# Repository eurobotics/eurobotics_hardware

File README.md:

# EuRobotics Engineering Hardware
Hardware del equipo Eurobotics Engineering para el desarrollo de robots participantes en Eurobot.

## Organización

 - Cada carpeta del repositorio se corresponde con una tarjeta.

 - En el root de cada capeta se encuentra el proyecto de desarrollo de la tarjeta (Eagle, Orcad, Altium...). Si es una tarjeta comercial la documentación dada por el fabricante.

 - Por lo general, los archivos de cada proyecto se nombran como MMMMM_rXX, donde XX es la revisión y MMMMM el nombre de la tarjeta. La modificaciones sobre tarjetas fabricadas se documentan añadiendo al nombre del fichero de diseño el sufijo _NNNN_rYY_, donde NNNN es el identificador de la modificacion y YY es el número revisión de la modificación. Por ejemplo: "mainboard_r15_eurobot2012_r1.pdf" es la modificación para eurobot 2012 con revisión 1 de la tarjeta mainboard correspondientes a la revisión 15 de los esquemas.

 - Cada carpeta de una tarjeta desarrollada puede contener las siguientes subcarpetas:
   + bom: listado de materiales.
   + cam: ficheros de fabricación y versión en pdf de versiones de tarjetas fabricadas o de modificaciones en placa realizadas para una edición concreta de Eurobot.

## dsPIC Protoboard

Tarjeta prototipo basada en microcontrolador dspic33. Desarrollada para Eurobot 2010. Diseñada en Eagle (sólo esquematicos). Fabricada sobre tarjeta de prototipos. Es la tarjeta que se utilizó en el robot prototipo, llamado Dumybot, con el que se portó las librerías Aversive.

### Características

* Control motores: DC, Dunkermotoren, servos, AX12.
* Comunicaciones: RS-232, BT, SPI, I2C
* Sensores: industriales, TTL, laser analógico y encoders en cuadratura
* GPIOS: puerto de expansión I2C de 16 E/S.

### Autor

Javier Baliñas Santos

## Mainboard V01/V02

Tarjeta principal del robot. Compuesta por dos microcontroladores dspic33 comunicados por I2C, un maestro y un esclavo. El maestro está pensado para implementar la navegación motriz y estrategia del robot, y el
esclavo para controlar la mecánica del robot.

Desarrollada para el robot de Eurobot 2010. Diseño en Eagle (esquemáticos y PCB). Tiene varios bugs documentados y solucionados en la versión 2.

La versión V02 de la tarjeta principal soluciona algunos errores de la versión V01. Desarrollada para Eurobot 2012 y utilizada en las ediciones posteriores.

### Características

* 3 motores Dunkermotoren
* 2 motores DC de 12V
* 1 solenoide 12V
* 1 relé
* 2 telémetros lásers
* 5 servos estándar
* 1 interfaz servos AX12
* 3 encoders con salida en cuadratura
* 7 sensores 12V
* 1 interfaz RS-232
* 2 interfaces Bluetooth (SPP)
* 1 conector para tarjeta de sensores _sensorboard_

### Autor

Javier Baliñas Santos

## Mainboard V03

Tercera versión de la tarjeta principal de los robots. Compuesta por un único un microcontrolador.

Desarrollada para Eurobot 2014 y utilizada en las ediciones posteriores.

### Características
* 3 motores DC de 12V
* 4 servos estándar
* 1 interfaz servos AX12
* 2 encoders con salida en cuadratura
* 1 encoder con salida en cuadratura (módulo x4, sin decodificación de signo)
* 16 E/S de 12/5V
* 2 entradas de captura de tiempo
* 1 interfaz RS-232/Bluetooth
* 1 interfaz I2C
* 1 interfaz SPI

### Autores

Diseño electrónico: Javier Baliñas Santos  
Diseño PCB: Rubén Espino San José

## Sensorboard

Tarjeta de expansión E/S digital por I2C (32 E/S). Desarrollada para Eurobot 2010 y reutilizada en las siguientes ediciones.

### Autor

Javier Baliñas Santos

## Swithboard

Tarjeta de distribución de alimentación de los robots. Permite activar de forma independiente las diferentes alimentaciones del robot: 24V, 12V y 5V. Desarrollada para Eurobot 2010 y reutilizada en las siguientes ediciones. Diseño en Eagle (esquemáticos y PCB).

### Autor

Javier Baliñas Santos

## Beaconboard

Electrónica de la baliza desarrollada para Eurobot 2010 por Diego Salazar. Permite el control de 1 motor DC con encoder en cuadratura, la lectura de 2 sensores de tipo Keyence y de 2 sensores opticos de herradura. Permite la comunicación por Bluetooth. Tiene bugs resueltos en placa, pero no todos documentados. Diseño en Orcad (esquemas y PCB).

### Autor

Diego Salazar Arcucci

## Vacuumboard

Tarjeta de control de hasta 4 electrovalvulas y 4 bombas de vacio.

### Autores

Diseño electrónico: Javier Baliñas Santos  
Diseño PCB: Rubén Espino San José

## M4 ATX

Fuente de alimentación mini ATX. Perminte un rango de alimentación variable y da salidas de +/-12V, 5V y 3.3V.  Se ha utilizado desde Eurobot 2010 para alimentar la electrónica del robot a partir de baterías. Es una tarjeta comercial.

## Licencia

Todos estos productos están liberados mediante [Creative Commons Attribution-ShareAlike 4.0 International License](http://creativecommons.org/licenses/by-sa/4.0/).  
_All these products are released under [Creative Commons Attribution-ShareAlike 4.0 International License](http://creativecommons.org/licenses/by-sa/4.0/)._

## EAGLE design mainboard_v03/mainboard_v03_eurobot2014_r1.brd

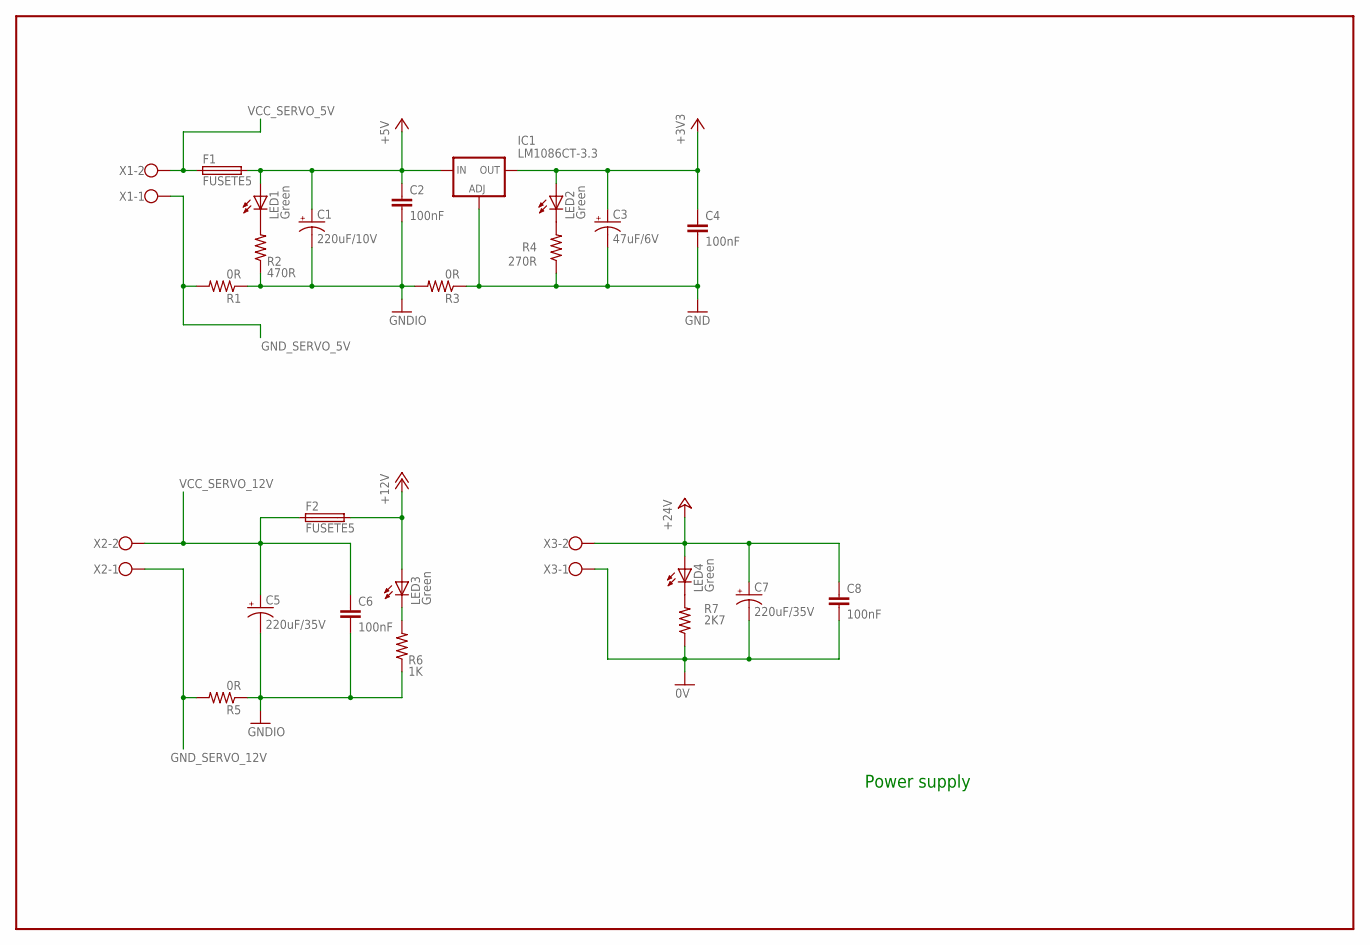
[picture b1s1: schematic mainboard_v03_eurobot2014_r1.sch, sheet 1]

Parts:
C1: 220uF/10V; E2,5-7
C2, C4, C6, C8: 100nF; C0805
C3: 47uF/6V; SMC_D
C5, C7: 220uF/35V; E5-10,5
F1, F2: FUSETE5; TE5
IC1: LM1086CT-3.3; 317TS
LED1, LED2, LED3, LED4: Green; CHIP-LED0805
R1, R3, R5: 0R; R0805
R2: 470R; R0805
R4: 270R; R0805
R6: 1K; R0805
R7: 2K7; R0805
X1, X2, X3: W237-02P; W237-132

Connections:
0V: C7.-, C8.2, R7.1, X3.1; also elsewhere on the board
+3V3: C3.+, C4.1, IC1.2 (OUT), LED2.A; also elsewhere on the board
+5V: C1.+, C2.1, F1.2, IC1.3 (IN), LED1.A; also elsewhere on the board
+12V: F2.2, LED3.A; also elsewhere on the board
+24V: C7.+, C8.1, LED4.A, X3.2; also elsewhere on the board
GND: C3.-, C4.2, IC1.1 (ADJ), R3.1, R4.1; also elsewhere on the board
GNDIO: C1.-, C2.2, C5.-, C6.2, R1.1, R2.1, R3.2, R5.1, R6.1; also elsewhere on the board
GND_SERVO_5V: R1.2, X1.1; also elsewhere on the board
GND_SERVO_12V: R5.2, X2.1; also elsewhere on the board
unnamed: LED1.C, R2.2
unnamed: LED2.C, R4.2
unnamed: LED3.C, R6.2
unnamed: LED4.C, R7.2
VCC_SERVO_5V: F1.1, X1.2; also elsewhere on the board
VCC_SERVO_12V: C5.+, C6.1, F2.1, X2.2; also elsewhere on the board

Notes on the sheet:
Power supply

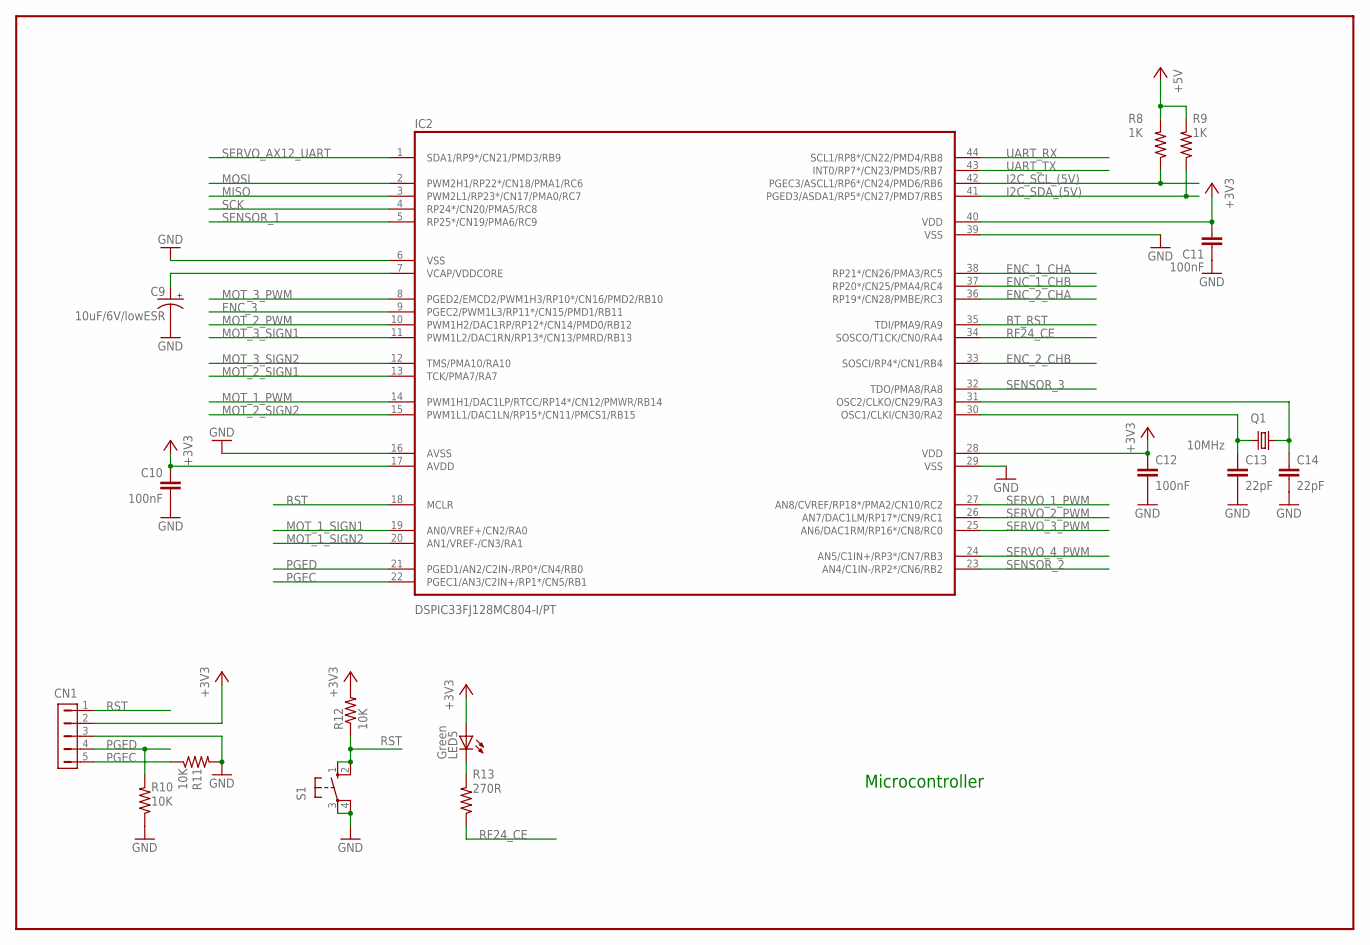
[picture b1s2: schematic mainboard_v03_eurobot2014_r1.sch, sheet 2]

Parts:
C9: 10uF/6V/lowESR; SMC_A
C10, C11, C12: 100nF; C0603
C13, C14: 22pF; C0805
CN1: HDR-1X5-SIP-100; SIP-100-5V
IC2: DSPIC33FJ128MC804-I/PT; TQFP44
LED5: Green; CHIP-LED0805
Q1: 10MHz; HC49UP
R8, R9: 1K; R0805
R10, R11, R12: 10K; R0805
R13: 270R; R0805
S1: 10-XX; B3F-10XX

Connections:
+3V3: C10.1, C11.1, C12.1, CN1.2, IC2.17 (AVDD), IC2.28 (VDD), IC2.40 (VDD), LED5.A, R12.2; also elsewhere on the board
+5V: R8.2, R9.2; also elsewhere on the board
BT_RST: IC2.35 (TDI/PMA9/RA9); also elsewhere on the board
ENC_1_CHA: IC2.38 (RP21*/CN26/PMA3/RC5); also elsewhere on the board
ENC_1_CHB: IC2.37 (RP20*/CN25/PMA4/RC4); also elsewhere on the board
ENC_2_CHA: IC2.36 (RP19*/CN28/PMBE/RC3); also elsewhere on the board
ENC_2_CHB: IC2.33 (SOSCI/RP4*/CN1/RB4); also elsewhere on the board
ENC_3: IC2.9 (PGEC2/PWM1L3/RP11*/CN15/PMD1/RB11); also elsewhere on the board
GND: C9.-, C10.2, C11.2, C12.2, C13.2, C14.2, CN1.3, IC2.6 (VSS), IC2.16 (AVSS), IC2.29 (VSS), IC2.39 (VSS), R10.1, R11.2, S1.3, S1.4 (P1); also elsewhere on the board
I2C_SCL_(5V): IC2.42 (PGEC3/ASCL1/RP6*/CN24/PMD6/RB6), R8.1; also elsewhere on the board
I2C_SDA_(5V): IC2.41 (PGED3/ASDA1/RP5*/CN27/PMD7/RB5), R9.1; also elsewhere on the board
MISO: IC2.3 (PWM2L1/RP23*/CN17/PMA0/RC7); also elsewhere on the board
MOSI: IC2.2 (PWM2H1/RP22*/CN18/PMA1/RC6); also elsewhere on the board
MOT_1_PWM: IC2.14 (PWM1H1/DAC1LP/RTCC/RP14*/CN12/PMWR/RB14); also elsewhere on the board
MOT_1_SIGN1: IC2.19 (AN0/VREF+/CN2/RA0); also elsewhere on the board
MOT_1_SIGN2: IC2.20 (AN1/VREF-/CN3/RA1); also elsewhere on the board
MOT_2_PWM: IC2.10 (PWM1H2/DAC1RP/RP12*/CN14/PMD0/RB12); also elsewhere on the board
MOT_2_SIGN1: IC2.13 (TCK/PMA7/RA7); also elsewhere on the board
MOT_2_SIGN2: IC2.15 (PWM1L1/DAC1LN/RP15*/CN11/PMCS1/RB15); also elsewhere on the board
MOT_3_PWM: IC2.8 (PGED2/EMCD2/PWM1H3/RP10*/CN16/PMD2/RB10); also elsewhere on the board
MOT_3_SIGN1: IC2.11 (PWM1L2/DAC1RN/RP13*/CN13/PMRD/RB13); also elsewhere on the board
MOT_3_SIGN2: IC2.12 (TMS/PMA10/RA10); also elsewhere on the board
unnamed: LED5.C, R13.2
unnamed: C14.1, IC2.31 (OSC2/CLKO/CN29/RA3), Q1.2
unnamed: C13.1, IC2.30 (OSC1/CLKI/CN30/RA2), Q1.1
unnamed: C9.+, IC2.7 (VCAP/VDDCORE)
PGEC: CN1.5, IC2.22 (PGEC1/AN3/C2IN+/RP1*/CN5/RB1), R11.1
PGED: CN1.4, IC2.21 (PGED1/AN2/C2IN-/RP0*/CN4/RB0), R10.2
RF24_CE: IC2.34 (SOSCO/T1CK/CN0/RA4), R13.1; also elsewhere on the board
RST: CN1.1, IC2.18 (MCLR), R12.1, S1.1 (S), S1.2 (S1)
SCK: IC2.4 (RP24*/CN20/PMA5/RC8); also elsewhere on the board
SENSOR_1: IC2.5 (RP25*/CN19/PMA6/RC9); also elsewhere on the board
SENSOR_2: IC2.23 (AN4/C1IN-/RP2*/CN6/RB2); also elsewhere on the board
SENSOR_3: IC2.32 (TDO/PMA8/RA8); also elsewhere on the board
SERVO_1_PWM: IC2.27 (AN8/CVREF/RP18*/PMA2/CN10/RC2); also elsewhere on the board
SERVO_2_PWM: IC2.26 (AN7/DAC1LM/RP17*/CN9/RC1); also elsewhere on the board
SERVO_3_PWM: IC2.25 (AN6/DAC1RM/RP16*/CN8/RC0); also elsewhere on the board
SERVO_4_PWM: IC2.24 (AN5/C1IN+/RP3*/CN7/RB3); also elsewhere on the board
SERVO_AX12_UART: IC2.1 (SDA1/RP9*/CN21/PMD3/RB9); also elsewhere on the board
UART_RX: IC2.44 (SCL1/RP8*/CN22/PMD4/RB8); also elsewhere on the board
UART_TX: IC2.43 (INT0/RP7*/CN23/PMD5/RB7); also elsewhere on the board

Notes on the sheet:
Microcontroller

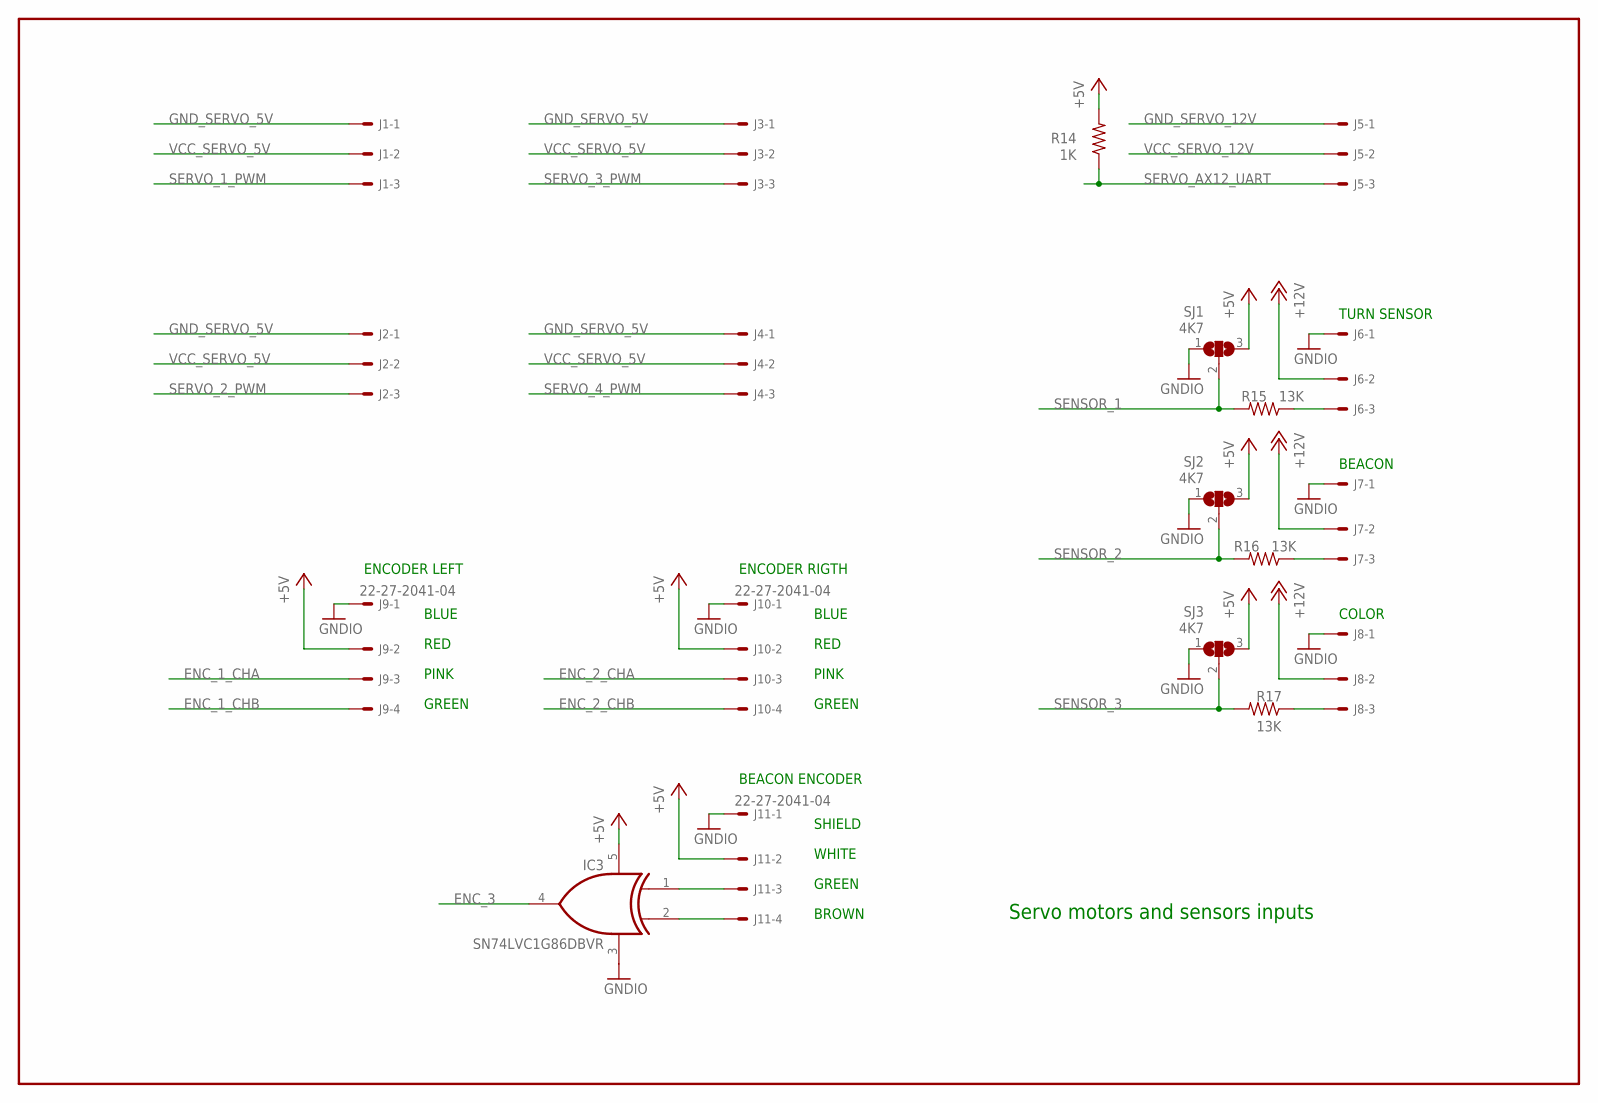
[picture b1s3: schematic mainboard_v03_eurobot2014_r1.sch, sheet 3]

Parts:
IC3: SN74LVC1G86DBVR; SOT23-5
J1, J2, J3, J4, J5, J6, J7, J8: 22-27-2031-03; 6410-03
J9, J10, J11: 22-27-2041-04; 6410-04
R14: 1K; R0805
R15, R16, R17: 13K; R0805
SJ1, SJ2, SJ3: 4K7; SJ_2

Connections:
+5V: IC3.5 (VCC), J9.2, J10.2, J11.2, R14.2, SJ1.3, SJ2.3, SJ3.3; also elsewhere on the board
+12V: J6.2, J7.2, J8.2; also elsewhere on the board
ENC_1_CHA: J9.3; also elsewhere on the board
ENC_1_CHB: J9.4; also elsewhere on the board
ENC_2_CHA: J10.3; also elsewhere on the board
ENC_2_CHB: J10.4; also elsewhere on the board
ENC_3: IC3.4 (O); also elsewhere on the board
GNDIO: IC3.3 (GND), J6.1, J7.1, J8.1, J9.1, J10.1, J11.1, SJ1.1, SJ2.1, SJ3.1; also elsewhere on the board
GND_SERVO_5V: J1.1, J2.1, J3.1, J4.1; also elsewhere on the board
GND_SERVO_12V: J5.1; also elsewhere on the board
unnamed: J6.3, R15.1
unnamed: IC3.1 (I0), J11.3
unnamed: IC3.2 (I1), J11.4
unnamed: J7.3, R16.1
unnamed: J8.3, R17.1
SENSOR_1: R15.2, SJ1.2; also elsewhere on the board
SENSOR_2: R16.2, SJ2.2; also elsewhere on the board
SENSOR_3: R17.2, SJ3.2; also elsewhere on the board
SERVO_1_PWM: J1.3; also elsewhere on the board
SERVO_2_PWM: J2.3; also elsewhere on the board
SERVO_3_PWM: J3.3; also elsewhere on the board
SERVO_4_PWM: J4.3; also elsewhere on the board
SERVO_AX12_UART: J5.3, R14.1; also elsewhere on the board
VCC_SERVO_5V: J1.2, J2.2, J3.2, J4.2; also elsewhere on the board
VCC_SERVO_12V: J5.2; also elsewhere on the board

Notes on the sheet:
Servo motors and sensors inputs
WHITE
GREEN
BROWN
SHIELD
BEACON ENCODER
ENCODER LEFT
ENCODER RIGTH
PINK
RED
BLUE
BEACON
TURN SENSOR
COLOR

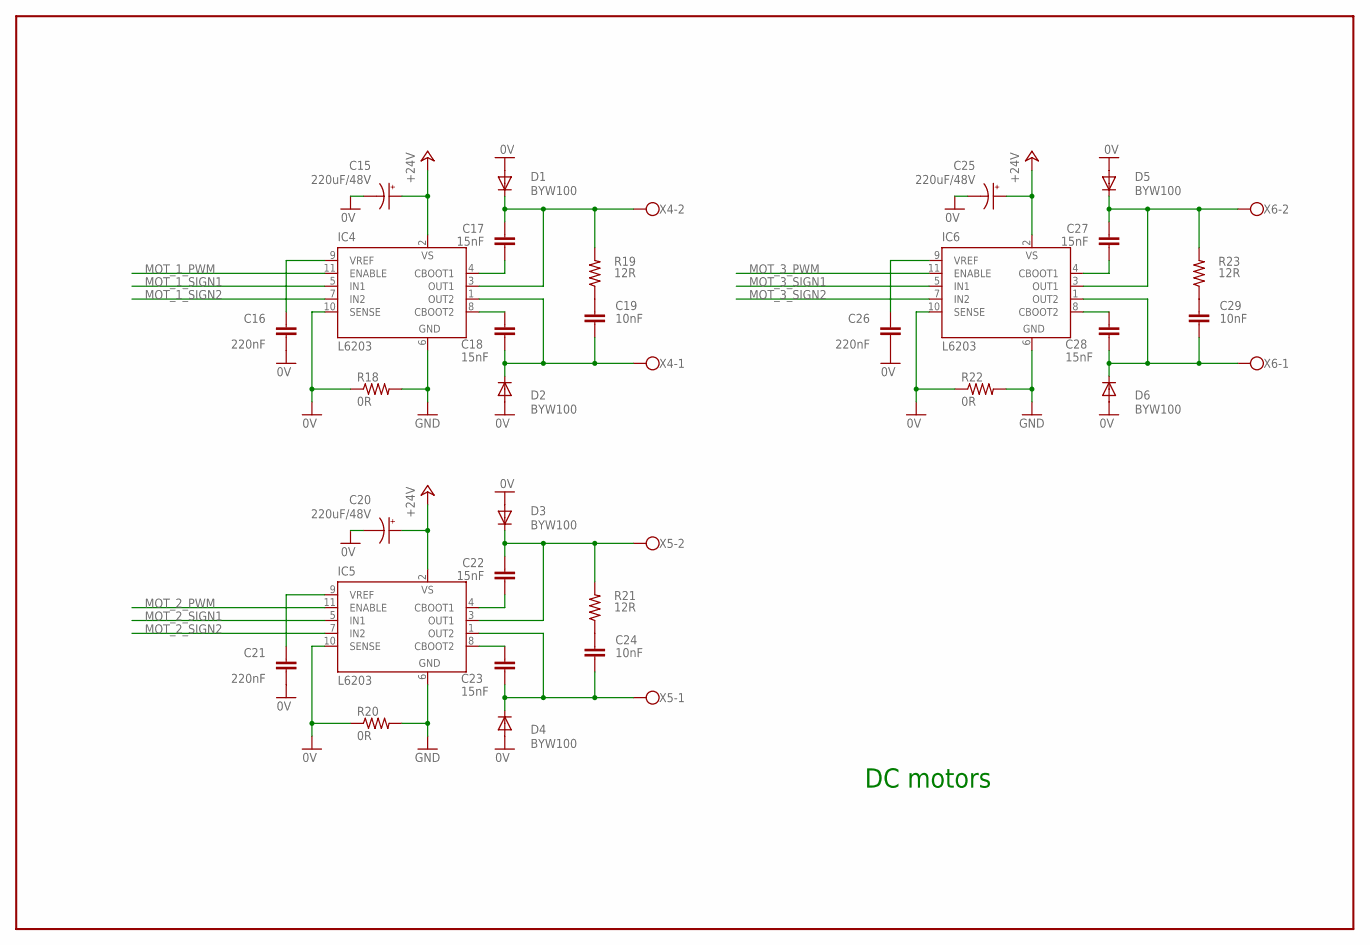
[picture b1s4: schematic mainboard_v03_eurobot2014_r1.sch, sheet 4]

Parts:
C15, C20, C25: 220uF/48V; E3,5-10
C16, C21, C26: 220nF; C0805
C17, C18, C22, C23, C27, C28: 15nF; C0805
C19, C24, C29: 10nF; C0805
D1, D2, D3, D4, D5, D6: BYW100; F126-10
IC4, IC5, IC6: L6203; MULTIWATT-11
R18, R20, R22: 0R; M0805
R19, R21, R23: 12R; M0805
X4, X5, X6: W237-02P; W237-132

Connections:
0V: C15.-, C16.2, C20.-, C21.2, C25.-, C26.2, D1.A, D2.A, D3.A, D4.A, D5.A, D6.A, IC4.10 (SENSE), IC5.10 (SENSE), IC6.10 (SENSE), R18.1, R20.1, R22.1; also elsewhere on the board
+24V: C15.+, C20.+, C25.+, IC4.2 (VS), IC5.2 (VS), IC6.2 (VS); also elsewhere on the board
GND: IC4.6 (GND), IC5.6 (GND), IC6.6 (GND), R18.2, R20.2, R22.2; also elsewhere on the board
MOT_1_PWM: IC4.11 (ENABLE); also elsewhere on the board
MOT_1_SIGN1: IC4.5 (IN1); also elsewhere on the board
MOT_1_SIGN2: IC4.7 (IN2); also elsewhere on the board
MOT_2_PWM: IC5.11 (ENABLE); also elsewhere on the board
MOT_2_SIGN1: IC5.5 (IN1); also elsewhere on the board
MOT_2_SIGN2: IC5.7 (IN2); also elsewhere on the board
MOT_3_PWM: IC6.11 (ENABLE); also elsewhere on the board
MOT_3_SIGN1: IC6.5 (IN1); also elsewhere on the board
MOT_3_SIGN2: IC6.7 (IN2); also elsewhere on the board
unnamed: C16.1, IC4.9 (VREF)
unnamed: C18.1, IC4.8 (CBOOT2)
unnamed: C17.1, IC4.4 (CBOOT1)
unnamed: C19.2, R19.1
unnamed: C17.2, D1.C, IC4.3 (OUT1), R19.2, X4.2
unnamed: C18.2, C19.1, D2.C, IC4.1 (OUT2), X4.1
unnamed: C21.1, IC5.9 (VREF)
unnamed: C26.1, IC6.9 (VREF)
unnamed: C28.1, IC6.8 (CBOOT2)
unnamed: C27.1, IC6.4 (CBOOT1)
unnamed: C23.1, IC5.8 (CBOOT2)
unnamed: C29.2, R23.1
unnamed: C22.1, IC5.4 (CBOOT1)
unnamed: C24.2, R21.1
unnamed: C22.2, D3.C, IC5.3 (OUT1), R21.2, X5.2
unnamed: C23.2, C24.1, D4.C, IC5.1 (OUT2), X5.1
unnamed: C27.2, D5.C, IC6.3 (OUT1), R23.2, X6.2
unnamed: C28.2, C29.1, D6.C, IC6.1 (OUT2), X6.1

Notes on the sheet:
DC motors

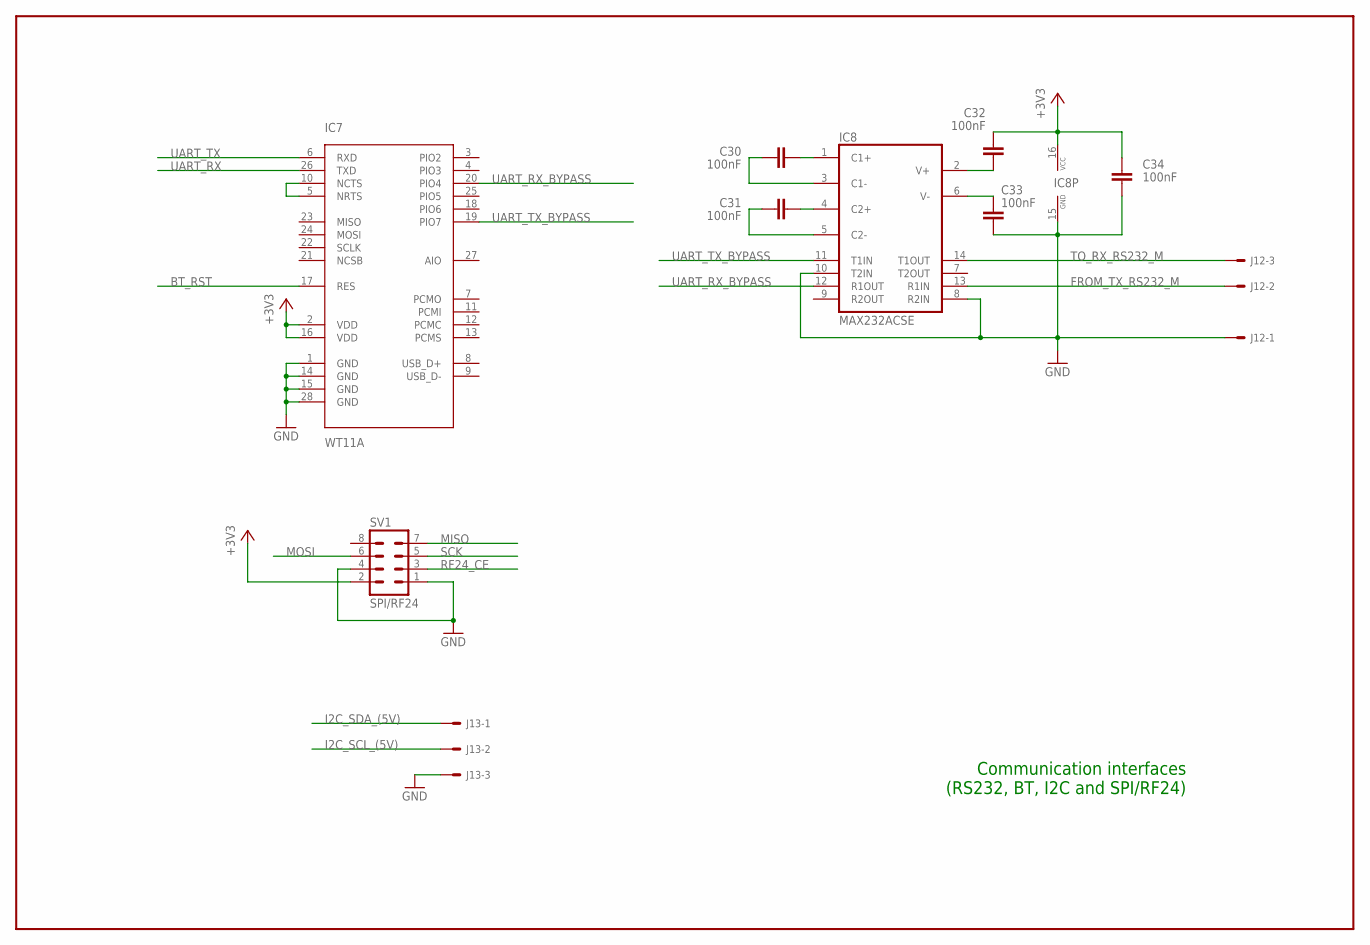
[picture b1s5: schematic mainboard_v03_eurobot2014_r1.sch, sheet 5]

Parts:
C30, C31, C32, C33, C34: 100nF; C0603
IC7: WT11A; WT11
IC8: MAX232ACSE; SO16
J12, J13: 22-27-2031-03; 6410-03
SV1: SPI/RF24; MA04-2

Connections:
+3V3: C32.2, C34.2, IC7.2 (VDD), IC7.16 (VDD), IC8.16 (VCC), SV1.2; also elsewhere on the board
BT_RST: IC7.17 (RES); also elsewhere on the board
FROM_TX_RS232_M: IC8.13 (R1IN), J12.2
GND: C33.1, C34.1, IC7.1 (GND), IC7.14 (GND), IC7.15 (GND), IC7.28 (GND), IC8.8 (R2IN), IC8.10 (T2IN), IC8.15 (GND), J12.1, J13.3, SV1.1, SV1.4; also elsewhere on the board
I2C_SCL_(5V): J13.2; also elsewhere on the board
I2C_SDA_(5V): J13.1; also elsewhere on the board
MISO: SV1.7; also elsewhere on the board
MOSI: SV1.6; also elsewhere on the board
unnamed: IC7.5 (NRTS), IC7.10 (NCTS)
unnamed: C30.2, IC8.1 (C1+)
unnamed: C30.1, IC8.3 (C1-)
unnamed: C31.2, IC8.4 (C2+)
unnamed: C31.1, IC8.5 (C2-)
unnamed: C32.1, IC8.2 (V+)
unnamed: C33.2, IC8.6 (V-)
RF24_CE: SV1.3; also elsewhere on the board
SCK: SV1.5; also elsewhere on the board
TO_RX_RS232_M: IC8.14 (T1OUT), J12.3
UART_RX: IC7.26 (TXD); also elsewhere on the board
UART_RX_BYPASS: IC7.20 (PIO4), IC8.12 (R1OUT)
UART_TX: IC7.6 (RXD); also elsewhere on the board
UART_TX_BYPASS: IC7.19 (PIO7), IC8.11 (T1IN)

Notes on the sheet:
Communication interfaces (RS232, BT, I2C and SPI/RF24)

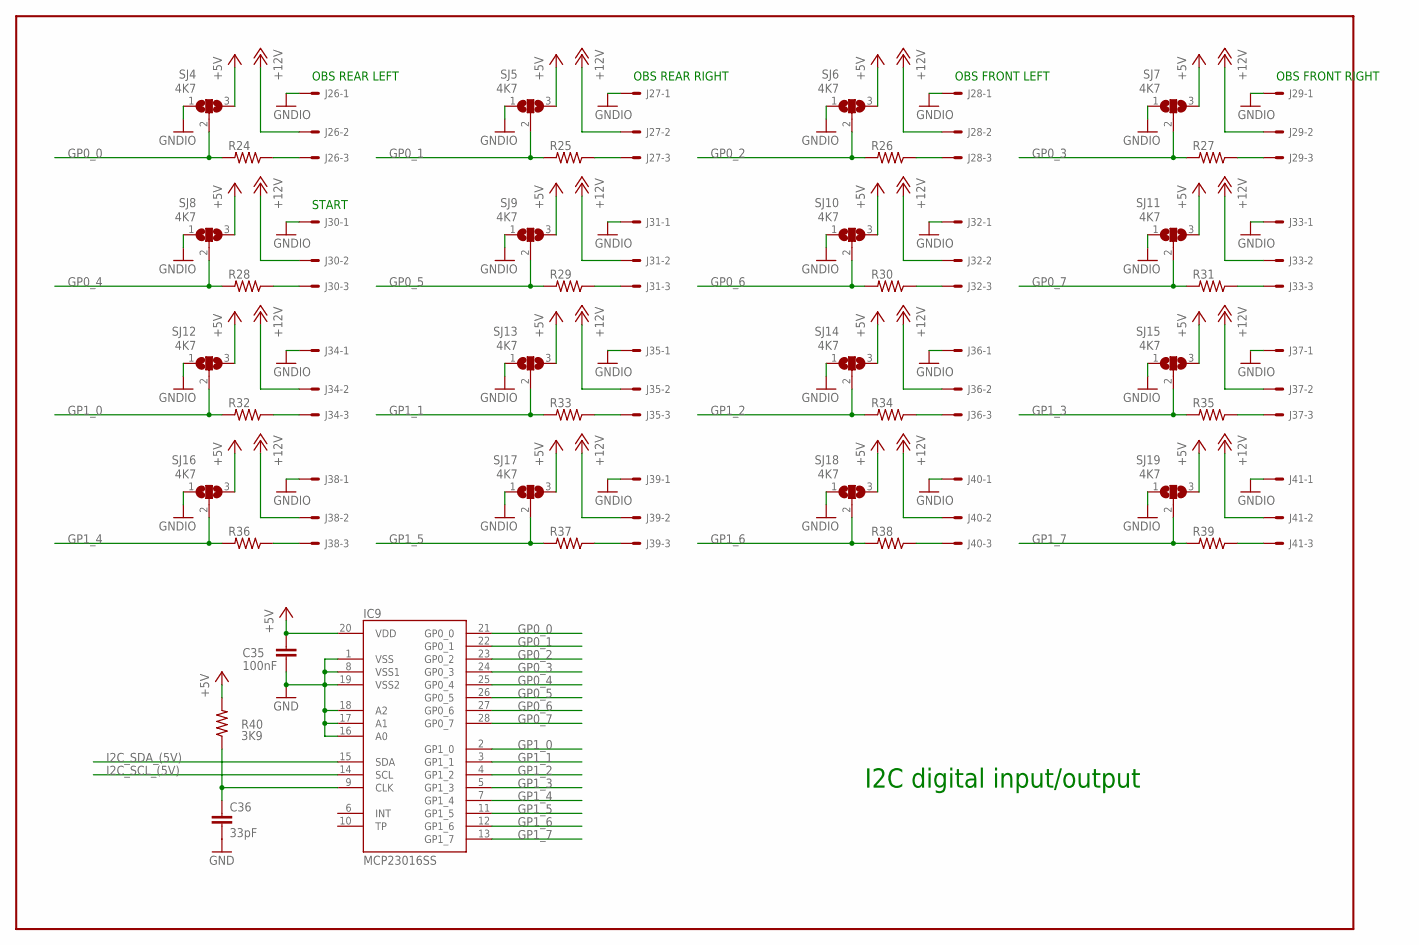
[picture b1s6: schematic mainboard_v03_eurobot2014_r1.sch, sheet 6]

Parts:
C35: 100nF; C0805
C36: 33pF; C0805
IC9: MCP23016SS; SSOP28
J26, J27, J28, J29, J30, J31, J32, J33, J34, J35, J36, J37, J38, J39, J40, J41: 22-27-2031-03; 6410-03
R24, R25, R26, R27, R28, R29, R30, R31, R32, R33, R34, R35, R36, R37, R38, R39: R-US_R0805; R0805
R40: 3K9; R0805
SJ4, SJ5, SJ6, SJ7, SJ8, SJ9, SJ10, SJ11, SJ12, SJ13, SJ14, SJ15, SJ16, SJ17, SJ18, SJ19: 4K7; SJ_2

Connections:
+5V: C35.1, IC9.20 (VDD), R40.2, SJ4.3, SJ5.3, SJ6.3, SJ7.3, SJ8.3, SJ9.3, SJ10.3, SJ11.3, SJ12.3, SJ13.3, SJ14.3, SJ15.3, SJ16.3, SJ17.3, SJ18.3, SJ19.3; also elsewhere on the board
+12V: J26.2, J27.2, J28.2, J29.2, J30.2, J31.2, J32.2, J33.2, J34.2, J35.2, J36.2, J37.2, J38.2, J39.2, J40.2, J41.2; also elsewhere on the board
GND: C35.2, C36.2, IC9.1 (VSS), IC9.8 (VSS1), IC9.16 (A0), IC9.17 (A1), IC9.18 (A2), IC9.19 (VSS2); also elsewhere on the board
GNDIO: J26.1, J27.1, J28.1, J29.1, J30.1, J31.1, J32.1, J33.1, J34.1, J35.1, J36.1, J37.1, J38.1, J39.1, J40.1, J41.1, SJ4.1, SJ5.1, SJ6.1, SJ7.1, SJ8.1, SJ9.1, SJ10.1, SJ11.1, SJ12.1, SJ13.1, SJ14.1, SJ15.1, SJ16.1, SJ17.1, SJ18.1, SJ19.1; also elsewhere on the board
GP0_0: IC9.21 (GP0_0), R24.2, SJ4.2
GP0_1: IC9.22 (GP0_1), R25.2, SJ5.2
GP0_2: IC9.23 (GP0_2), R26.2, SJ6.2
GP0_3: IC9.24 (GP0_3), R27.2, SJ7.2
GP0_4: IC9.25 (GP0_4), R28.2, SJ8.2
GP0_5: IC9.26 (GP0_5), R29.2, SJ9.2
GP0_6: IC9.27 (GP0_6), R30.2, SJ10.2
GP0_7: IC9.28 (GP0_7), R31.2, SJ11.2
GP1_0: IC9.2 (GP1_0), R32.2, SJ12.2
GP1_1: IC9.3 (GP1_1), R33.2, SJ13.2
GP1_2: IC9.4 (GP1_2), R34.2, SJ14.2
GP1_3: IC9.5 (GP1_3), R35.2, SJ15.2
GP1_4: IC9.7 (GP1_4), R36.2, SJ16.2
GP1_5: IC9.11 (GP1_5), R37.2, SJ17.2
GP1_6: IC9.12 (GP1_6), R38.2, SJ18.2
GP1_7: IC9.13 (GP1_7), R39.2, SJ19.2
I2C_SCL_(5V): IC9.14 (SCL); also elsewhere on the board
I2C_SDA_(5V): IC9.15 (SDA); also elsewhere on the board
unnamed: J26.3, R24.1
unnamed: J30.3, R28.1
unnamed: J27.3, R25.1
unnamed: J31.3, R29.1
unnamed: J34.3, R32.1
unnamed: J38.3, R36.1
unnamed: J35.3, R33.1
unnamed: J39.3, R37.1
unnamed: J40.3, R38.1
unnamed: J36.3, R34.1
unnamed: J37.3, R35.1
unnamed: J41.3, R39.1
unnamed: J32.3, R30.1
unnamed: J33.3, R31.1
unnamed: J29.3, R27.1
unnamed: J28.3, R26.1
unnamed: C36.1, IC9.9 (CLK), R40.1

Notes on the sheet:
I2C digital input/output
OBS FRONT LEFT
OBS FRONT RIGHT
OBS REAR LEFT
OBS REAR RIGHT
START

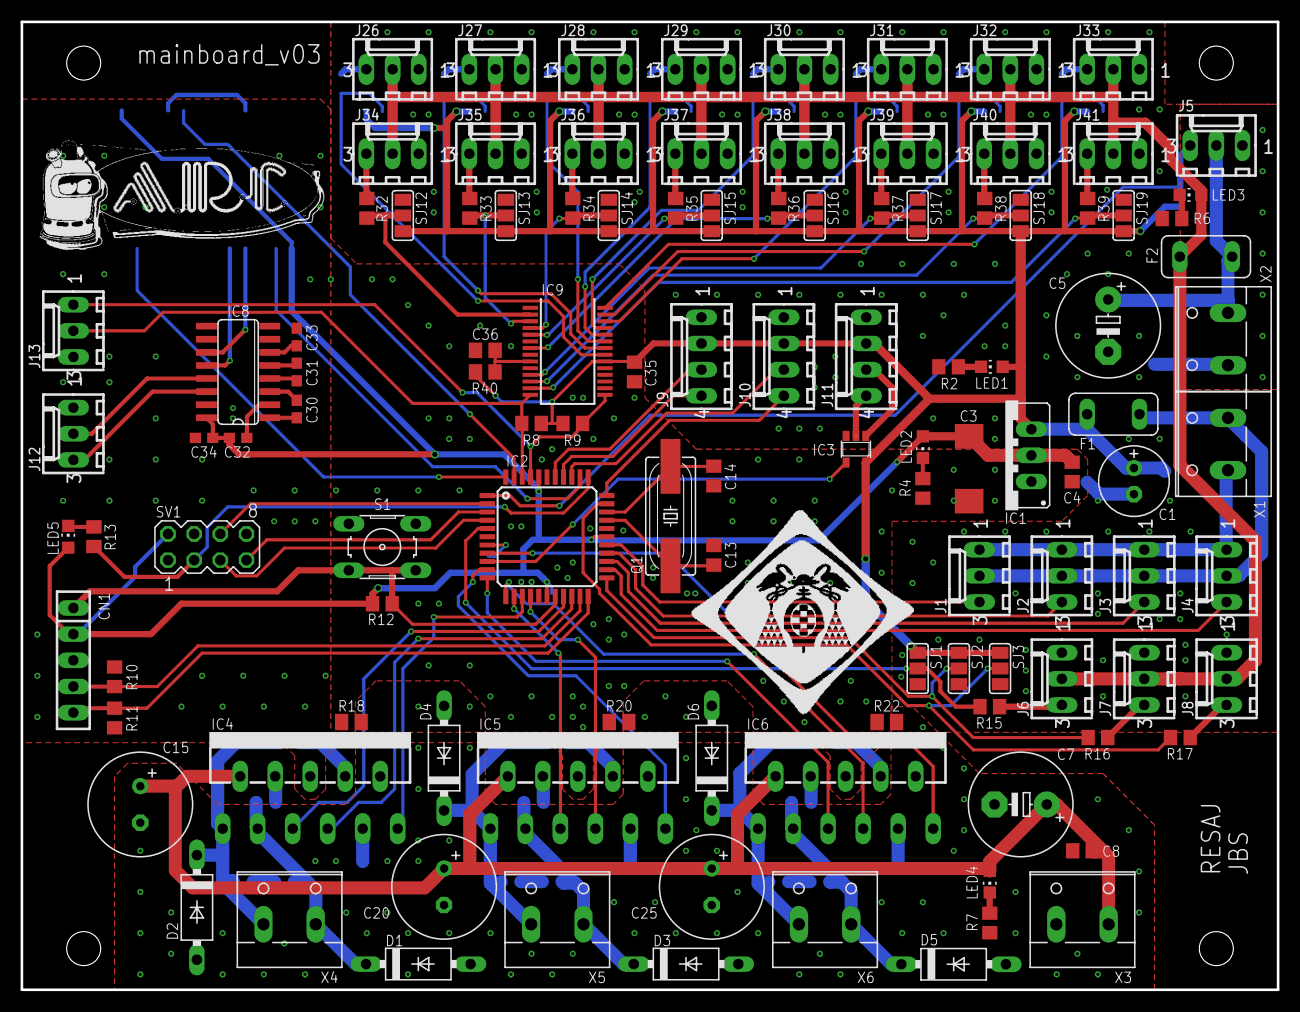
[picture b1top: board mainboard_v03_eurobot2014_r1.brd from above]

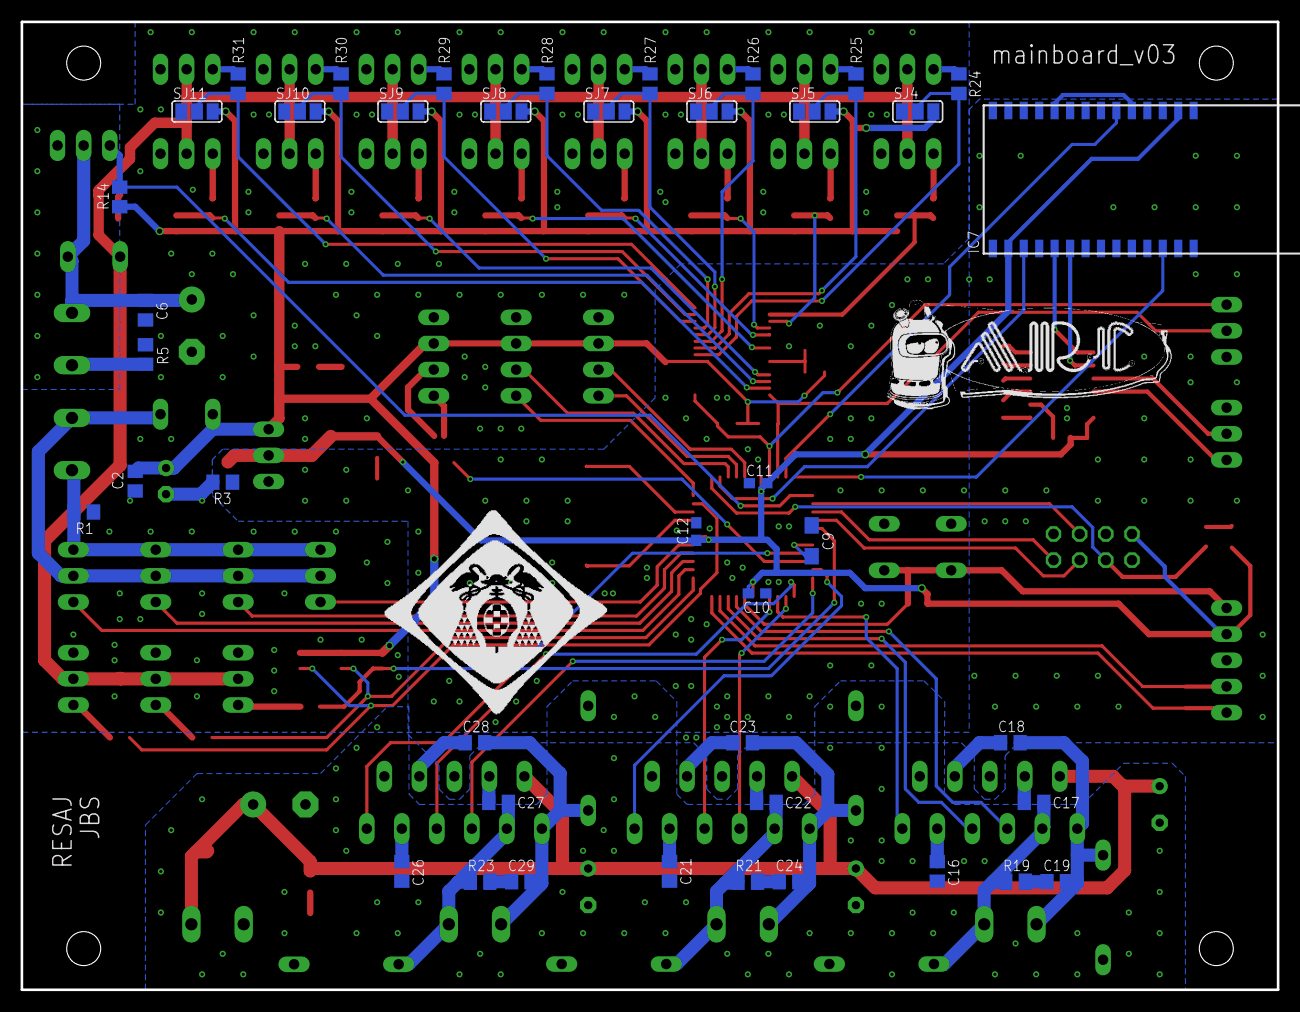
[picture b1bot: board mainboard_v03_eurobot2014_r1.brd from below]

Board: 2 copper layers, 122.0 x 94.0 mm, 160 parts (44 on the bottom side), 120 nets.

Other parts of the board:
U$1, U$2: LOGO_ARC_28MM
U$3, U$4: LOGO_IEEE_22MM

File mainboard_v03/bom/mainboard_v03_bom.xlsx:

Qty | Parts | Columna1 | Value | Package | Description | Manufacturer | Manufacture Part # | Supplier | Supplier Part # | Min Qty | Price (EUR) | Ext. Qty | Ext. Price
1 | C1 |  | 220uF/10V | E2,5-7 | CONDENSADOR ELECTROLITICO / 10V / PASO 2.5mm |  |  | symbol |  |  |  | 1 | 0
8 | C10, C11, C12, C30, C31, C32, C33, C34 |  | 100nF | C0603 | CONDENSADOR CERAMICO / 50V / SMD 0603 |  |  |  |  |  |  | 8 | 0
2 | C13, C14 |  | 22pF | C0805 | CONDENSADOR CERAMICO / 50V / SMD 0805 |  |  |  |  |  |  | 2 | 0
3 | C15, C20, C25 |  | 220uF/48V | E3,5-10 | CONDENSADOR ELECTROLITICO / 48V / PASO 3.5mm |  |  | symbol |  |  |  | 3 | 0
3 | C16, C21, C26 |  | 220nF | C0805 | CONDENSADOR CERAMICO / 50V / SMD 0805 |  |  |  |  |  |  | 3 | 0
6 | C17, C18, C22, C23, C27, C28 |  | 15nF | C0805 | CONDENSADOR CERAMICO / 50V / SMD 0805 |  |  |  |  |  |  | 6 | 0
3 | C19, C24, C29 |  | 10nF | C0805 | CONDENSADOR CERAMICO / 50V / SMD 0805 |  |  |  |  |  |  | 3 | 0
5 | C2, C4, C6, C8, C35 |  | 100nF | C0805 | CONDENSADOR CERAMICO / 50V / SMD 0805 |  |  |  |  |  |  | 5 | 0
1 | C3 |  | 47uF/6V | SMC_D | CONDENSADOR TANTALO / 6V / SMD SMC-D |  |  | symbol |  |  |  | 1 | 0
1 | C36 |  | 33pF | C0805 | CONDENSADOR CERAMICO / 50V / SMD 0805 |  |  |  |  |  |  | 1 | 0
2 | C5, C7 |  | 220uF/35V | E5-10,5 | CONDENSADOR ELECTROLITICO / 35V / PASO 5mm |  |  | symbol |  |  |  | 2 | 0
1 | C9 |  | 10uF/6V/lowESR | SMC_A | CONDENSADOR TANTALO / 6V / SMD SMC-A |  |  | symbol |  |  |  | 1 | 0
1 | CN1 |  |  | SIP-100-5V | TIRA DE PINES MACHO ACODADA / PCB |  |  |  |  |  |  | 1 | 0
6 | D1, D2, D3, D4, D5, D6 |  | BYW100 | F126-10 | DIODO DE RECUPERACIÓN RÁPIDA |  |  |  |  |  |  | 6 | 0
2 | F1, F2 |  | FUSETE5 | TE5 | FUSIBLE REARMABLE / 1A / PASO 5mm |  |  |  |  |  |  | 2 | 0
1 | IC1 |  | LM1086CT-3.3 | 317TS | REGULADOR DE VOLTAJE |  |  |  |  |  |  | 1 | 0
1 | IC2 |  | DSPIC33FJ128MC804-I/PT | TQFP44 | MICROCONTROLADOR / TQFP44 |  |  |  |  |  |  | 1 | 0
1 | IC3 |  | SN74LVC1G86DBVR | SOT23-5 | PUERTA LOGICA XOR / SOT23 |  |  |  |  |  |  | 1 | 0
3 | IC4, IC5, IC6 |  | L6203 | MULTIWATT-11 | DRIVER PUENTE EN H MOSFET |  |  |  |  |  |  | 3 | 0
1 | IC7 |  | WT11A | WT11 | MODULO BLUETOOTH |  |  |  |  |  |  | 1 | 0
1 | IC8 |  | MAX232ACSE | SO16 | TRASNCEIVER RS-232 / SO16 |  |  |  |  |  |  | 1 | 0
1 | IC9 |  | MCP23016SS | SSOP28 | EXPANSON DE PUERTOS I2C / SSOP28 |  |  |  |  |  |  | 1 | 0
26 | J1, J2, J3, J4, J5, J6, J7, J8, J12, J13, J26, J27, J28, J29, J30, J31, J32, J3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 |  |  | 6410-03 | CONECTOR MOLEX / 3 VIAS / PCB VERTICAL / PASO 2.54mm |  |  |  |  |  |  | 26 | 0
26 | J1, J2, J3, J4, J5, J6, J7, J8, J12, J13, J26, J27, J28, J29, J30, J31, J32, J3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 |  |  | 6410-03 | CONECTOR MOLEX / 3 VIAS / CABLE / PASO 2.54mm |  |  |  |  |  |  | 26 | 0
3 | J9, J10, J11 |  | 22-27-2041-04 | 6410-04 | CONECTOR MOLEX / 4 VIAS / PCB VERTICAL / PASO 2.54mm |  |  |  |  |  |  | 3 | 0
5 | LED1, LED2, LED3, LED4, LED5 |  | Green | CHIP-LED0805 | LED VERDE / SMD 0805 |  |  |  |  |  |  | 5 | 0
1 | Q1 |  | 10MHz | HC49UP | CRYSTAL 10.000MHz / SMD HC49UP |  |  |  |  |  |  | 1 | 0
3 | R1, R3, R5 |  | 0R | R0805 | RESISTENCIA / 5% / 0.1W / SMD 0805 |  |  |  |  |  |  | 3 | 0
3 | R10, R11, R12 |  | 10K | R0805 | RESISTENCIA / 5% / 0.1W / SMD 0805 |  |  |  |  |  |  | 3 | 0
3 | R15, R16, R17 |  | 13K | R0805 | RESISTENCIA / 5% / 0.1W / SMD 0805 |  |  |  |  |  |  | 3 | 0
3 | R18, R20, R22 |  | 0R | M0805 | RESISTENCIA / 5% / 0.1W / SMD 0805 |  |  |  |  |  |  | 3 | 0
3 | R19, R21, R23 |  | 12R | M0805 | RESISTENCIA / 5% / 0.1W / SMD 0805 |  |  |  |  |  |  | 3 | 0
1 | R2 |  | 470R | R0805 | RESISTENCIA / 5% / 0.1W / SMD 0805 |  |  |  |  |  |  | 1 | 0
16 | R24, R25, R26, R27, R28, R29, R30, R31, R32, R33, R34, R35, R36, R37, R38, R39 |  |  | R0805 | RESISTENCIA / 5% / 0.1W / SMD 0805 |  |  |  |  |  |  | 16 | 0
2 | R4, R13 |  | 270R | R0805 | RESISTENCIA / 5% / 0.1W / SMD 0805 |  |  |  |  |  |  | 2 | 0
1 | R40 |  | 3K9 | R0805 | RESISTENCIA / 5% / 0.1W / SMD 0805 |  |  |  |  |  |  | 1 | 0
4 | R6, R8, R9, R14 |  | 1K | R0805 | RESISTENCIA / 5% / 0.1W / SMD 0805 |  |  |  |  |  |  | 4 | 0
1 | R7 |  | 2K7 | R0805 | RESISTENCIA / 5% / 0.1W / SMD 0805 |  |  |  |  |  |  | 1 | 0
1 | S1 |  |  | B3F-10XX | PULSADOR CUELLO CORTO / TIPO DPST (DOBLE CIRCUITO PULSACION ÚNICA) |  |  |  |  |  |  | 1 | 0
19 | SJ1, SJ2, SJ3, SJ4, SJ5, SJ6, SJ7, SJ8, SJ9, SJ10, SJ11, SJ12, SJ13, SJ14, SJ15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 |  | 4K7 | SJ_2 | RESISTENCIA / 5% / 0.1W / SMD 0805 |  |  |  |  |  |  | 19 | 0
1 | SV1 |  | SPI/RF24 | MA04-2 | TIRA DE PINES HEMBRA / 2 FILAS X 4 PINES / PCB |  |  |  |  |  |  | 1 | 0
6 | X1, X2, X3, X4, X5, X6 |  |  | W237-132 | CONNECTOR TIPO CLEMA ENCHUFABLE / PCB VERTICAL / PASO 5.08mm |  |  |  |  |  |  | 6 | 0
6 | X1, X2, X3, X4, X5, X6 |  |  | W237-132 | CONNECTOR TIPO CLEMA ENCHUFABLE / CABLE / PASO 5.08mm |  |  |  |  |  |  | 6 | 0

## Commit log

2016-03-01 Creado fichero de ignorados.
2016-03-01 Creado fichero readme.
2016-03-01 Añadida fuente de alimentación ATX y completado README.
2016-03-01 Completado README.
2016-03-01 Añadido el resto de tarjetas.
2016-03-01 Añadida licencia.
2016-03-01 Añadida imagen de licencia CC.
2016-03-07 Añadidas fotos de las tarjetas.
2016-03-10 Nueva organizacion en carpeta docs. Aladidas nuevas fotos y actualizado readme.
2016-03-10 Dimensiones de imagenes re-escaladas, actualizado readme.
2016-03-10 Fotos de tarjetas modificadas.
2016-03-10 Nueva foto de la sensorboard.
2016-03-10 Modificado dimensiones de la foto de la switchboard.
2016-10-02 Mejoras en readme
